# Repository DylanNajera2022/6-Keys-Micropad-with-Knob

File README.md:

# 6-Keys-Micropad-with-Knob
This is my simple six-button micropad with its knob, it's a simple thing I made in a few hours and I plan to improve its case in the future.

# Firmware:
The firmware is still in progress and the screen has not yet been integrated. So far, the code only integrates the knob that increases/decreases the volume and pauses the content when pressed. The micropad has these six programmed functions: undo, redo, copy, paste, quick save, and switch screen.

# Schematic and PCB:
Making the PCB and the schematic was a headache because it was the first time I ever used KiCad, so I had a lot of errors that I had to fix and had to redo the PCB and the schematic several times.

# Case:
Making the case was also a headache because it was also the first time I used Fusion360, so I was very lost, but by following tutorials I managed to make an acceptable case, although I plan to improve it in the future.

# Finished Macropad:
This is the finished macropad. In Hack Club's blueprint, you can see a description of the whole process of making it. https://blueprint.hackclub.com/projects/4851

# BOM:
- 6x Cherry MX Switches
- 1x XIAO RP2040
- 6x Blank DSA Keycaps
- 4x M3x16 Bolt
- 4x M3 Heatset
- 1x EC11 Rotary encoder with switch
- 1x 0.91 Oled display

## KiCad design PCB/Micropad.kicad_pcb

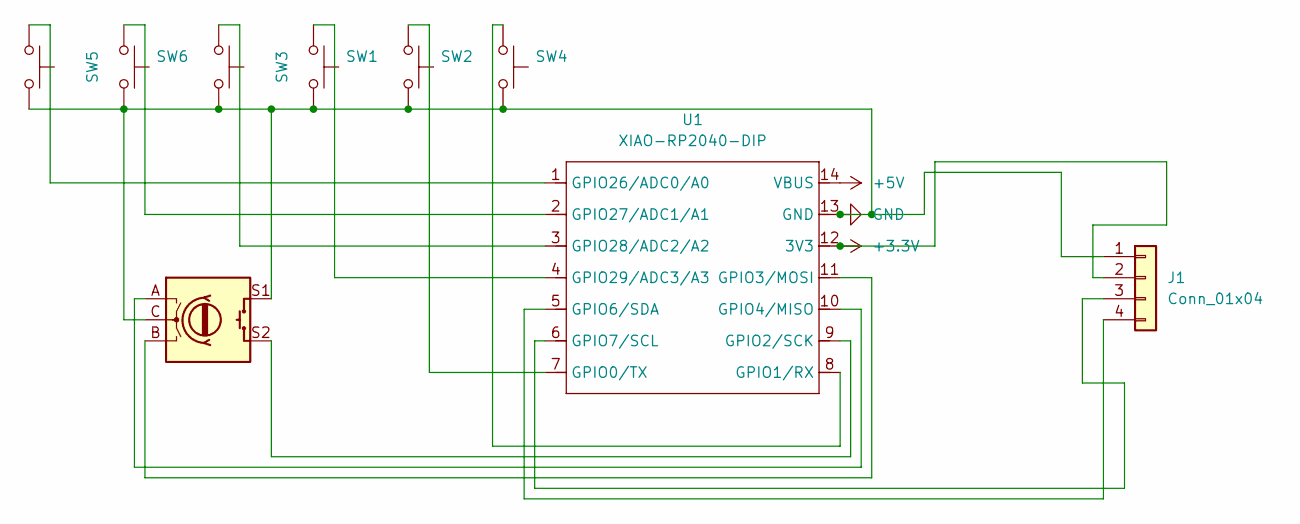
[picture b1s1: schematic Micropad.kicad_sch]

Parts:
J1: Conn_01x04
SW1, SW2, SW3, SW4, SW5, SW6: SW_Push; SW_Cherry_MX_1.00u_PCB
SW7: RotaryEncoder_Switch; RotaryEncoder_Alps_EC11E-Switch_Vertical_H20mm
U1: XIAO-RP2040-DIP

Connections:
+3.3V: J1.2, U1.12 (3V3)
+5V: U1.14 (VBUS)
GND: J1.1, SW1.2, SW2.2, SW3.2, SW4.2, SW5.2, SW6.2, SW7.C, SW7.S1, U1.13 (GND)
unnamed: J1.3, U1.6 (GPIO7/SCL)
unnamed: J1.4, U1.5 (GPIO6/SDA)
unnamed: SW2.1, U1.7 (GPIO0/TX)
unnamed: SW4.1, U1.8 (GPIO1/RX)
unnamed: SW7.S2, U1.9 (GPIO2/SCK)
unnamed: SW7.B, U1.11 (GPIO3/MOSI)
unnamed: SW7.A, U1.10 (GPIO4/MISO)
unnamed: SW5.1, U1.1 (GPIO26/ADC0/A0)
unnamed: SW6.1, U1.2 (GPIO27/ADC1/A1)
unnamed: SW3.1, U1.3 (GPIO28/ADC2/A2)
unnamed: SW1.1, U1.4 (GPIO29/ADC3/A3)

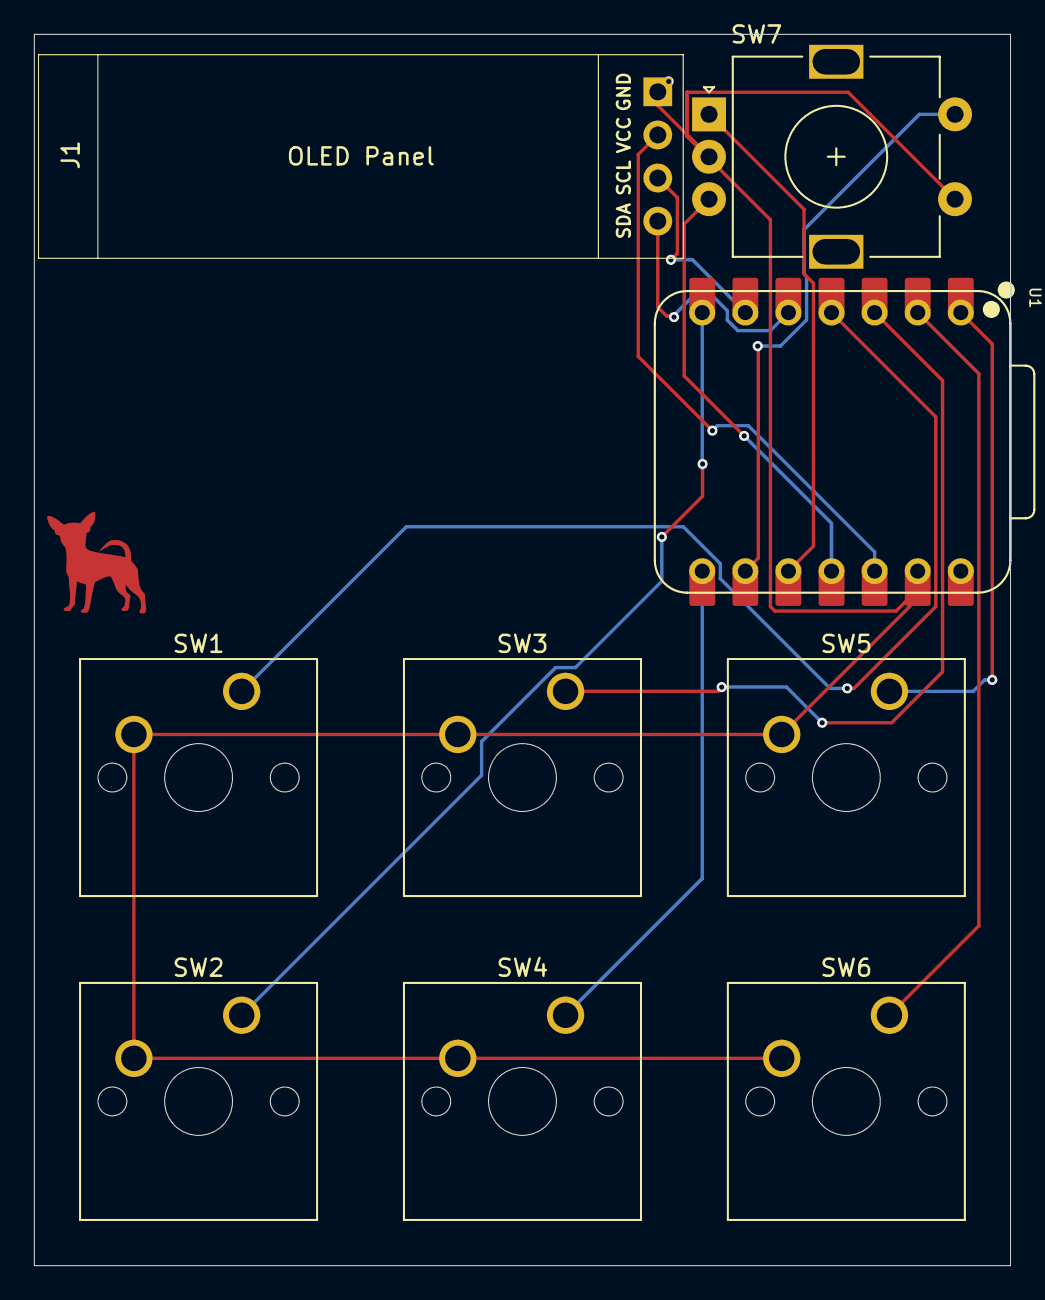
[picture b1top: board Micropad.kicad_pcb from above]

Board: 2 copper layers, 57.5 x 72.6 mm, 9 parts (0 on the bottom side), 13 nets.

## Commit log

2025-12-06 Enhance README with project details and images
    Expanded description of the micropad project, including details about firmware, schematic, PCB, case design, and bill of materials.
2025-12-07 Revise images and update BOM in README
    Updated images and BOM details in README.
2025-12-07 Add images to case section in README
    Added two new images to the case section in the README.
2026-02-22 Add OLED display module and optimize memory handling
    Refactor keyboard configuration to include OLED display module and optimize memory usage.
2026-02-22 Document finished macropad and add images
    Added section about the finished macropad with images and a link to Hack Club's blueprint.
2026-02-22 Fix header formatting in README.md
